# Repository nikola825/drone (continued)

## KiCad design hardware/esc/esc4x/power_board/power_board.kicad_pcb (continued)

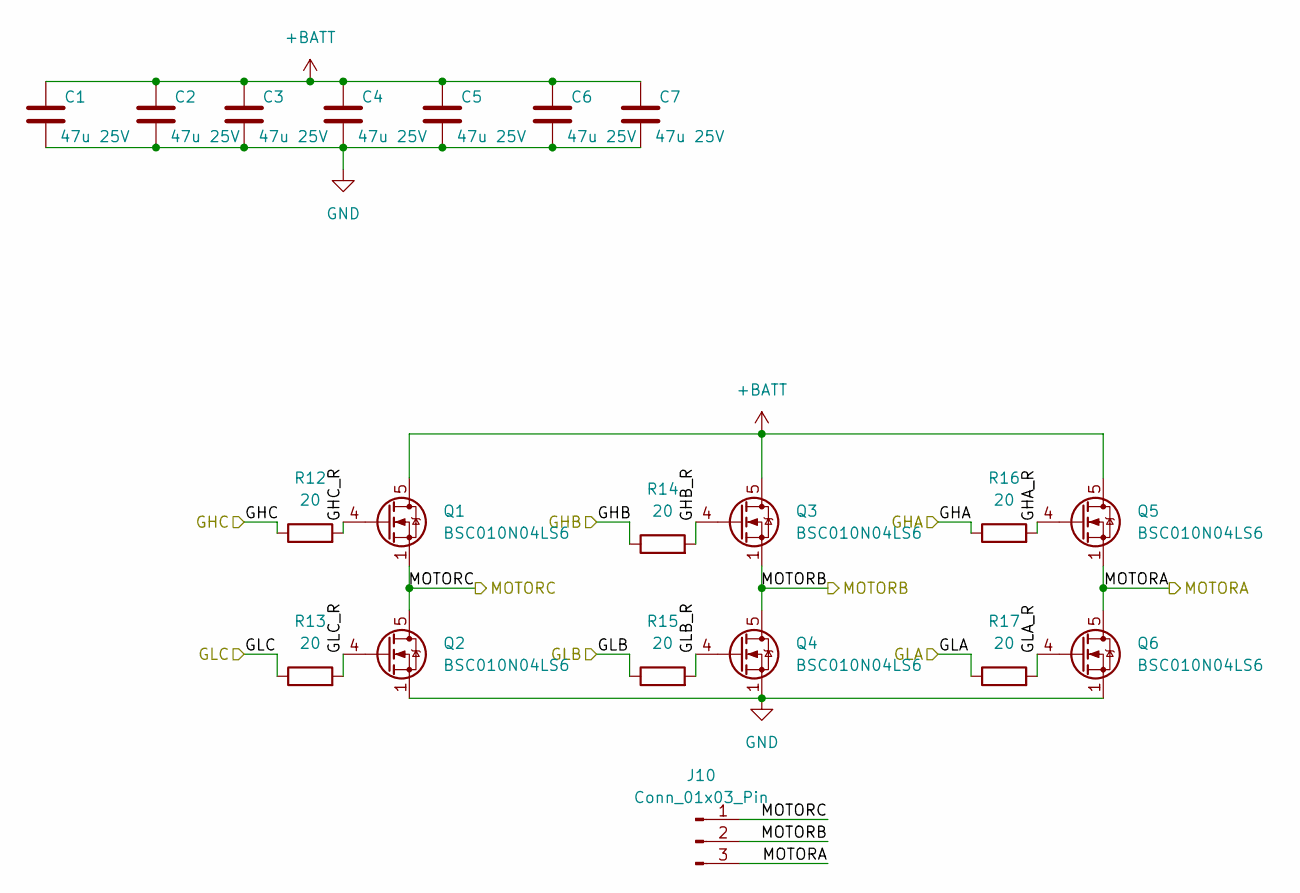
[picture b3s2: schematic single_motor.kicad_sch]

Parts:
C1, C2, C3, C4, C5, C6, C7: 47u 25V; C_1206_3216Metric
J10: Conn_01x03_Pin; EscMotorConnector
Q1, Q2, Q3, Q4, Q5, Q6: BSC010N04LS6; InfineonTdson8FL
R12, R13, R14, R15, R16, R17: 20; R_0402_1005Metric

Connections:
+BATT: C1.1, C2.1, C3.1, C4.1, C5.1, C6.1, C7.1, Q1.5 (D), Q3.5 (D), Q5.5 (D); also elsewhere on the board
/EscMotor1/GHA: R16.1; also elsewhere on the board
/EscMotor1/GHA_R: Q5.4 (G), R16.2
/EscMotor1/GHB: R14.1; also elsewhere on the board
/EscMotor1/GHB_R: Q3.4 (G), R14.2
/EscMotor1/GHC: R12.1; also elsewhere on the board
/EscMotor1/GHC_R: Q1.4 (G), R12.2
/EscMotor1/GLA: R17.1; also elsewhere on the board
/EscMotor1/GLA_R: Q6.4 (G), R17.2
/EscMotor1/GLB: R15.1; also elsewhere on the board
/EscMotor1/GLB_R: Q4.4 (G), R15.2
/EscMotor1/GLC: R13.1; also elsewhere on the board
/EscMotor1/GLC_R: Q2.4 (G), R13.2
/EscMotor1/MOTORA: J10.3, Q5.1 (S), Q6.5 (D); also elsewhere on the board
/EscMotor1/MOTORB: J10.2, Q3.1 (S), Q4.5 (D); also elsewhere on the board
/EscMotor1/MOTORC: J10.1, Q1.1 (S), Q2.5 (D); also elsewhere on the board
GND: C1.2, C2.2, C3.2, C4.2, C5.2, C6.2, C7.2, Q2.1 (S), Q4.1 (S), Q6.1 (S); also elsewhere on the board

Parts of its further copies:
C12, C13, C14, C15, C16, C17, C18, C19, C20, C21, C22, C23, C24, C25, C26, C27, C28, C29, C30, C31, C32: 47u 25V; C_1206_3216Metric
J4, J5, J6: Conn_01x03_Pin; EscMotorConnector
Q7, Q8, Q9, Q10, Q11, Q12, Q13, Q14, Q15, Q16, Q17, Q18, Q19, Q20, Q21, Q22, Q23, Q24: BSC010N04LS6; InfineonTdson8FL
R1, R2, R3, R4, R5, R6, R7, R8, R9, R10, R11, R18, R19, R20, R21, R22, R23, R24: 20; R_0402_1005Metric

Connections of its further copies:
+BATT: C12.1, C13.1, C14.1, C15.1, C16.1, C17.1, C18.1, C19.1, C20.1, C21.1, C22.1, C23.1, C24.1, C25.1, C26.1, C27.1, C28.1, C29.1, C30.1, C31.1, C32.1, Q7.5 (D), Q9.5 (D), Q11.5 (D), Q13.5 (D), Q15.5 (D), Q17.5 (D), Q19.5 (D), Q21.5 (D), Q23.5 (D); also elsewhere on the board
/EscMotor2/GHA: R5.1; also elsewhere on the board
/EscMotor2/GHA_R: Q11.4 (G), R5.2
/EscMotor2/GHB: R3.1; also elsewhere on the board
/EscMotor2/GHB_R: Q9.4 (G), R3.2
/EscMotor2/GHC: R1.1; also elsewhere on the board
/EscMotor2/GHC_R: Q7.4 (G), R1.2
/EscMotor2/GLA: R6.1; also elsewhere on the board
/EscMotor2/GLA_R: Q12.4 (G), R6.2
/EscMotor2/GLB: R4.1; also elsewhere on the board
/EscMotor2/GLB_R: Q10.4 (G), R4.2
/EscMotor2/GLC: R2.1; also elsewhere on the board
/EscMotor2/GLC_R: Q8.4 (G), R2.2
/EscMotor2/MOTORA: J4.3, Q11.1 (S), Q12.5 (D); also elsewhere on the board
/EscMotor2/MOTORB: J4.2, Q9.1 (S), Q10.5 (D); also elsewhere on the board
/EscMotor2/MOTORC: J4.1, Q7.1 (S), Q8.5 (D); also elsewhere on the board
/EscMotor3/GHA: R11.1; also elsewhere on the board
/EscMotor3/GHA_R: Q17.4 (G), R11.2
/EscMotor3/GHB: R9.1; also elsewhere on the board
/EscMotor3/GHB_R: Q15.4 (G), R9.2
/EscMotor3/GHC: R7.1; also elsewhere on the board
/EscMotor3/GHC_R: Q13.4 (G), R7.2
/EscMotor3/GLA: R18.1; also elsewhere on the board
/EscMotor3/GLA_R: Q18.4 (G), R18.2
/EscMotor3/GLB: R10.1; also elsewhere on the board
/EscMotor3/GLB_R: Q16.4 (G), R10.2
/EscMotor3/GLC: R8.1; also elsewhere on the board
/EscMotor3/GLC_R: Q14.4 (G), R8.2
/EscMotor3/MOTORA: J5.3, Q17.1 (S), Q18.5 (D); also elsewhere on the board
/EscMotor3/MOTORB: J5.2, Q15.1 (S), Q16.5 (D); also elsewhere on the board
/EscMotor3/MOTORC: J5.1, Q13.1 (S), Q14.5 (D); also elsewhere on the board
/EscMotor4/GHA: R23.1; also elsewhere on the board
/EscMotor4/GHA_R: Q23.4 (G), R23.2
/EscMotor4/GHB: R21.1; also elsewhere on the board
/EscMotor4/GHB_R: Q21.4 (G), R21.2
/EscMotor4/GHC: R19.1; also elsewhere on the board
/EscMotor4/GHC_R: Q19.4 (G), R19.2
/EscMotor4/GLA: R24.1; also elsewhere on the board
/EscMotor4/GLA_R: Q24.4 (G), R24.2
/EscMotor4/GLB: R22.1; also elsewhere on the board
/EscMotor4/GLB_R: Q22.4 (G), R22.2
/EscMotor4/GLC: R20.1; also elsewhere on the board
/EscMotor4/GLC_R: Q20.4 (G), R20.2
/EscMotor4/MOTORA: J6.3, Q23.1 (S), Q24.5 (D); also elsewhere on the board
/EscMotor4/MOTORB: J6.2, Q21.1 (S), Q22.5 (D); also elsewhere on the board
/EscMotor4/MOTORC: J6.1, Q19.1 (S), Q20.5 (D); also elsewhere on the board
GND: C12.2, C13.2, C14.2, C15.2, C16.2, C17.2, C18.2, C19.2, C20.2, C21.2, C22.2, C23.2, C24.2, C25.2, C26.2, C27.2, C28.2, C29.2, C30.2, C31.2, C32.2, Q8.1 (S), Q10.1 (S), Q12.1 (S), Q14.1 (S), Q16.1 (S), Q18.1 (S), Q20.1 (S), Q22.1 (S), Q24.1 (S); also elsewhere on the board

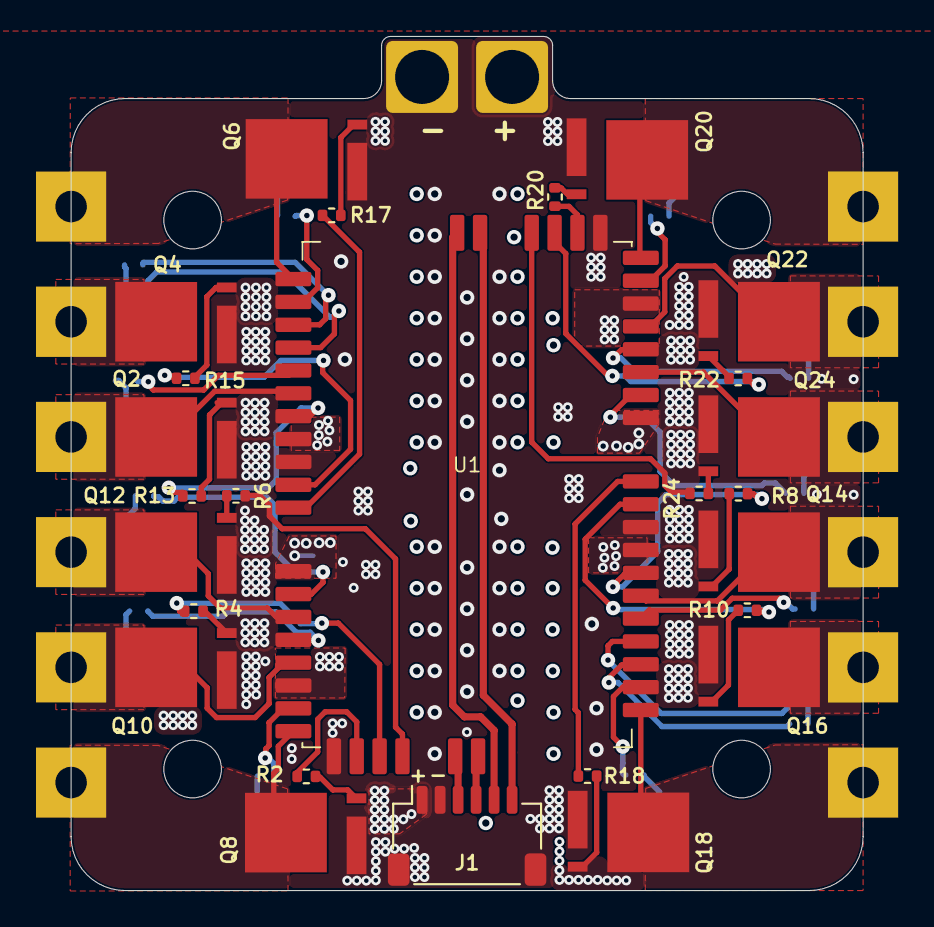
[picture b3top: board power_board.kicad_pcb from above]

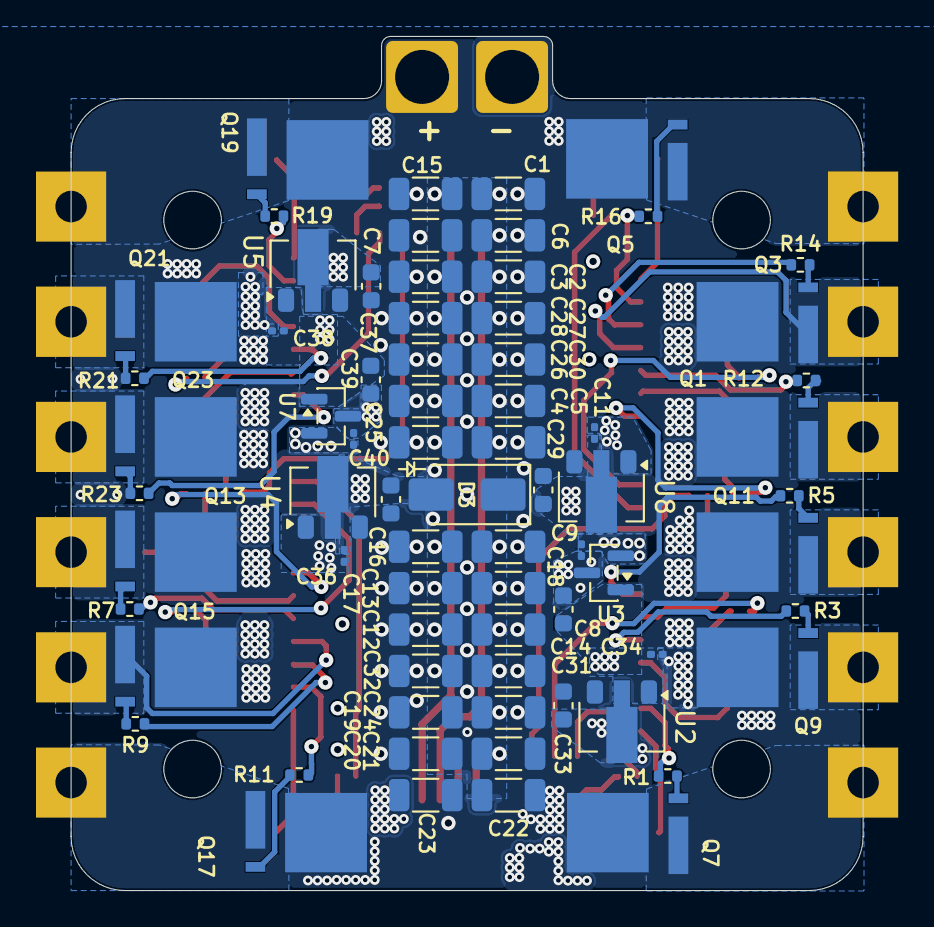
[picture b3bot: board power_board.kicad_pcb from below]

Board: 4 copper layers, 44.0 x 47.5 mm, 107 parts (71 on the bottom side), 72 nets.

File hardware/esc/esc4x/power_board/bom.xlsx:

|  |  | xxxx xxxx xxxxx xxPCS BOM (Sample Bill of Materials)
Item # | *Designator | *Qty | Manufacturer | *Mfg Part # | Description / Value | *Package/Footprint | Type | Your Instructions / Notes
1 | C1, C2, C3, C4, C5, C6, C7, C12, C13, C14, C15, C16, C17, C18, C19, C20, C21, C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 | 28 | TDK | C3216X5R1E476M160AC | CAP CER 47uF 25V X5R 1206 | 1206 | SMD
2 | C8, C10, C33, C35, C37, C39 | 6 | Murata | GCJ188R71E105KA01D | CAP CER 1uF 25V X7R 0603 | 0603 | SMD
3 | C9, C11, C34, C36, C38, C40 | 6 | Murata | GRM033R61A105ME44D | CAP CER 1uF 10V X5R 0201 | 0201 | SMD
4 | D3 | 1 | Yageo | SMAJ26A-HP6AT | VS Diodes SMAJ DO214AC 26V 42.1V AEC-Q101 | DO-214AC | SMD
5 | J1 | 1 | JST | SM06B-SRSS-TB | JST SH Headers SMT SIDE 6-pin | JST SH 6-pin header | SMD
6 | Q1, Q2, Q3, Q4, Q5, Q6, Q7, Q8, Q9, Q10, Q11, Q12, Q13, Q14, Q15, Q16, Q17, Q18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 | 24 | Infineon | BSC010N04LS6 | N-Channel 40 V 100A 3W Surface Mount PG-TDSON-8-6 | TDSON-8-FL | SMD
7 | R1, R2, R3, R4, R5, R6, R7, R8, R9, R10, R11, R12, R13, R14, R15, R16, R17, R18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 | 24 | Yageo | RC0402FR-0720RL | RES 20 OHM 0.067W 1% 0402 | 0402 | SMD
8 | U2, U4, U5, U8 | 4 | Diodes incorporated | AP7381-50Y-13 | LDO Voltage Regulators 150mA 5V | SOT-89-3 | SMD
9 | U3, U7 | 2 | Diodes incorporated | AP7381-33SA-7 | LDO Voltage Regulator 100mA 3.3V | SOT-23-3 | SMD
Need a quick and accurante quote? Need an efficient production? Please read SMT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
Click for Instructions on How to Create a BOM

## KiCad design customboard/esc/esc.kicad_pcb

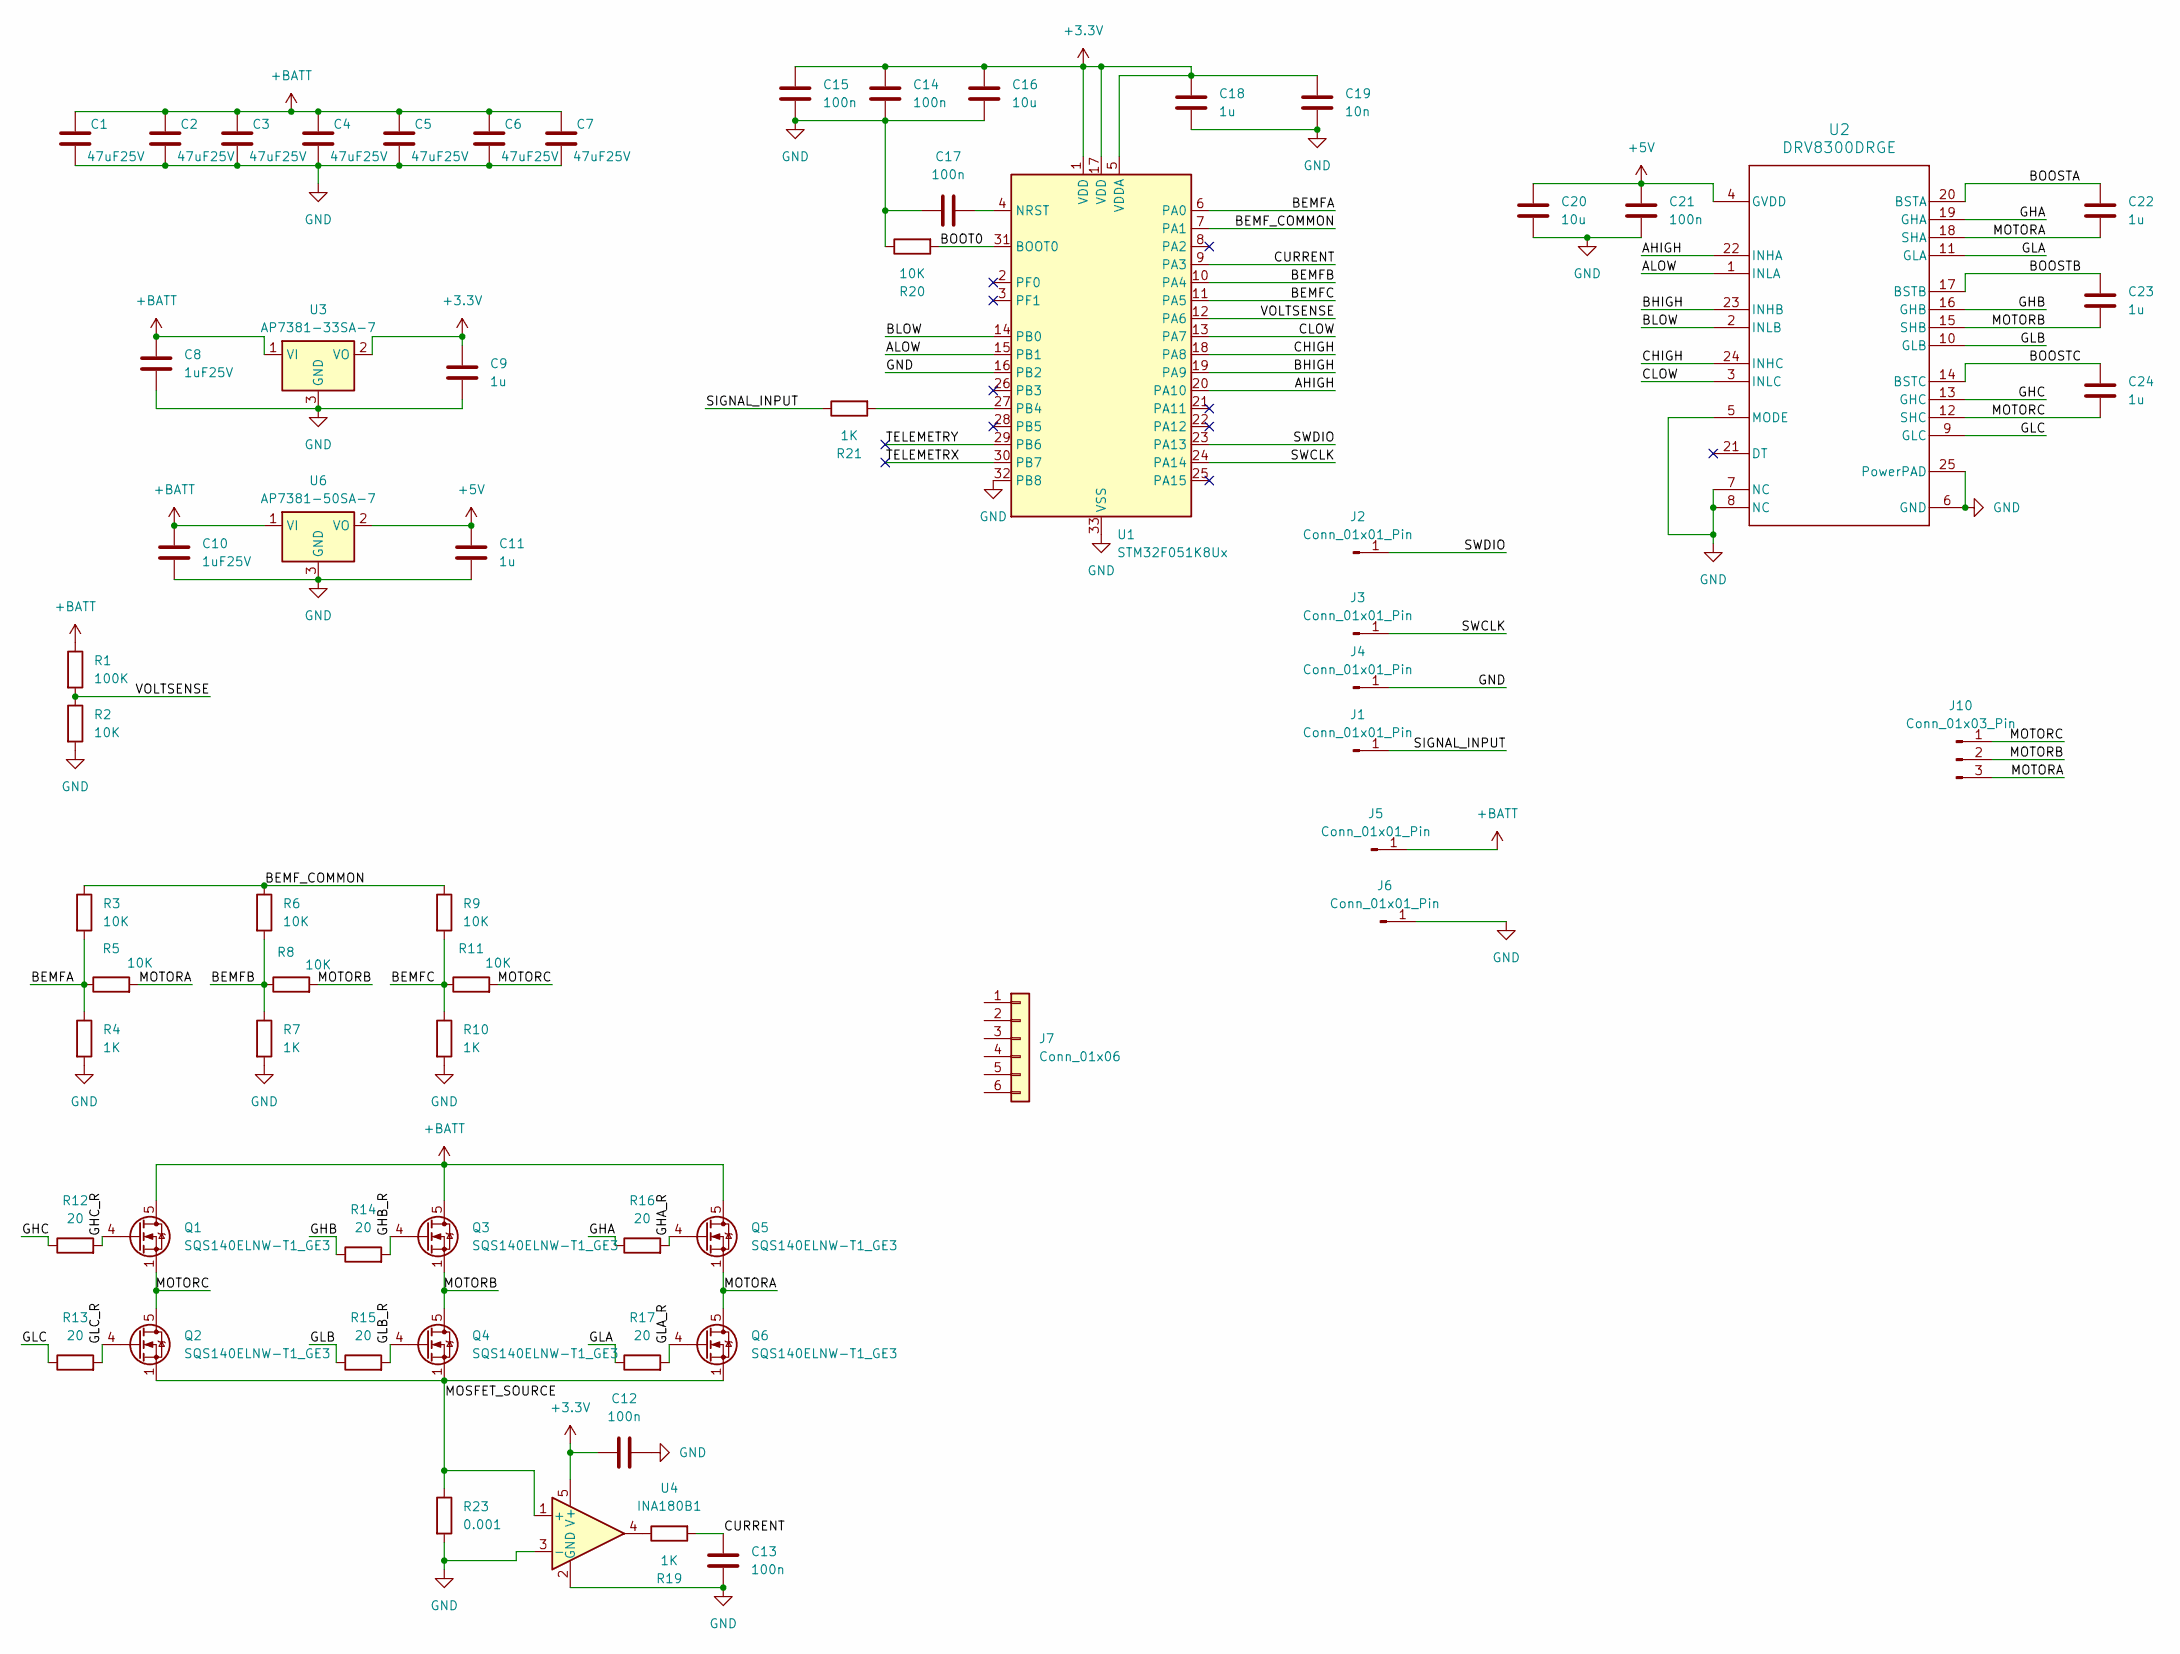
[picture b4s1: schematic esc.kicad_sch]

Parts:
C1, C2, C3, C4, C5, C6, C7: 47uF25V; C_1206_3216Metric
C8, C10: 1uF25V; C_0603_1608Metric
C9, C11, C18, C22, C23, C24: 1u; C_0201_0603Metric
C12, C13, C14, C15, C17, C21: 100n; C_0201_0603Metric
C16, C20: 10u; C_0402_1005Metric
C19: 10n; C_0201_0603Metric
J1, J2, J3, J4: Conn_01x01_Pin; SolderWirePad_1x01_SMD_1x2mm
J5, J6: Conn_01x01_Pin; EscBatteryConnector
J7: Conn_01x06; PinHeader_1x06_P1.27mm_Vertical
J10: Conn_01x03_Pin; EscMotorConnector
Q1, Q2, Q3, Q4, Q5, Q6: SQS140ELNW-T1_GE3; Vishay_PowerPAK_1212-8_Single
R1: 100K; R_0402_1005Metric
R2: 10K; R_0402_1005Metric
R3, R5, R6, R8, R9, R11, R20: 10K; R_0201_0603Metric
R4, R7, R10, R19, R21: 1K; R_0201_0603Metric
R12, R13, R14, R15, R16, R17: 20; R_0402_1005Metric
R23: 0.001; R_2512_6332Metric
U1: STM32F051K8Ux; QFN-32-1EP_5x5mm_P0.5mm_EP3.45x3.45mm-Custom
U2: DRV8300DRGE; VQFN-24-1EP_4x4mm_P0.5mm_EP2.45x2.45mm_ThermalVias-Custom
U3: AP7381-33SA-7; SOT-23
U4: INA180B1; SOT-23-5
U6: AP7381-50SA-7; SOT-23

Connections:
+3.3V: C9.1, C12.1, C14.2, C15.2, C16.2, C18.1, C19.2, U1.1 (VDD), U1.5 (VDDA), U1.17 (VDD), U3.2 (VO), U4.5 (V+)
+5V: C11.1, C20.2, C21.2, U2.4 (GVDD), U6.2 (VO)
+BATT: C1.1, C2.1, C3.1, C4.1, C5.1, C6.1, C7.1, C8.1, C10.1, J5.1, Q1.5 (D), Q3.5 (D), Q5.5 (D), R1.1, U3.1 (VI), U6.1 (VI)
/AHIGH: U1.20 (PA10), U2.22 (INHA)
/ALOW: U1.15 (PB1), U2.1 (INLA)
/BEMFA: R3.2, R4.1, R5.1, U1.6 (PA0)
/BEMFB: R6.2, R7.1, R8.1, U1.10 (PA4)
/BEMFC: R9.2, R10.1, R11.1, U1.11 (PA5)
/BEMF_COMMON: R3.1, R6.1, R9.1, U1.7 (PA1)
/BHIGH: U1.19 (PA9), U2.23 (INHB)
/BLOW: U1.14 (PB0), U2.2 (INLB)
/BOOSTA: C22.2, U2.20 (BSTA)
/BOOSTB: C23.2, U2.17 (BSTB)
/BOOSTC: C24.2, U2.14 (BSTC)
/BOOT0: R20.2, U1.31 (BOOT0)
/CHIGH: U1.18 (PA8), U2.24 (INHC)
/CLOW: U1.13 (PA7), U2.3 (INLC)
/CURRENT: C13.2, R19.2, U1.9 (PA3)
/GHA: R16.1, U2.19 (GHA)
/GHA_R: Q5.4 (G), R16.2
/GHB: R14.1, U2.16 (GHB)
/GHB_R: Q3.4 (G), R14.2
/GHC: R12.1, U2.13 (GHC)
/GHC_R: Q1.4 (G), R12.2
/GLA: R17.1, U2.11 (GLA)
/GLA_R: Q6.4 (G), R17.2
/GLB: R15.1, U2.10 (GLB)
/GLB_R: Q4.4 (G), R15.2
/GLC: R13.1, U2.9 (GLC)
/GLC_R: Q2.4 (G), R13.2
/MOSFET_SOURCE: Q2.1 (S), Q2.2 (S), Q2.3 (S), Q4.1 (S), Q4.2 (S), Q4.3 (S), Q6.1 (S), Q6.2 (S), Q6.3 (S), R23.1, U4.1 (+)
/MOTORA: C22.1, J10.3, Q5.1 (S), Q5.2 (S), Q5.3 (S), Q6.5 (D), R5.2, U2.18 (SHA)
/MOTORB: C23.1, J10.2, Q3.1 (S), Q3.2 (S), Q3.3 (S), Q4.5 (D), R8.2, U2.15 (SHB)
/MOTORC: C24.1, J10.1, Q1.1 (S), Q1.2 (S), Q1.3 (S), Q2.5 (D), R11.2, U2.12 (SHC)
/SIGNAL_INPUT: J1.1, R21.1
/SWCLK: J3.1, U1.24 (PA14)
/SWDIO: J2.1, U1.23 (PA13)
/TELEMETRX: U1.30 (PB7)
/TELEMETRY: U1.29 (PB6)
/VOLTSENSE: R1.2, R2.1, U1.12 (PA6)
GND: C1.2, C2.2, C3.2, C4.2, C5.2, C6.2, C7.2, C8.2, C9.2, C10.2, C11.2, C12.2, C13.1, C14.1, C15.1, C16.1, C17.2, C18.2, C19.1, C20.1, C21.1, J4.1, J6.1, R2.2, R4.2, R7.2, R10.2, R20.1, R23.2, U1.16 (PB2), U1.32 (PB8), U1.33 (VSS), U2.5 (MODE), U2.6 (GND), U2.7 (NC), U2.8 (NC), U2.25 (PowerPAD), U3.3 (GND), U4.2 (GND), U4.3 (-), U6.3 (GND)
unnamed: R19.1, U4.4
unnamed: C17.1, U1.4 (NRST)
unnamed: R21.2, U1.27 (PB4)

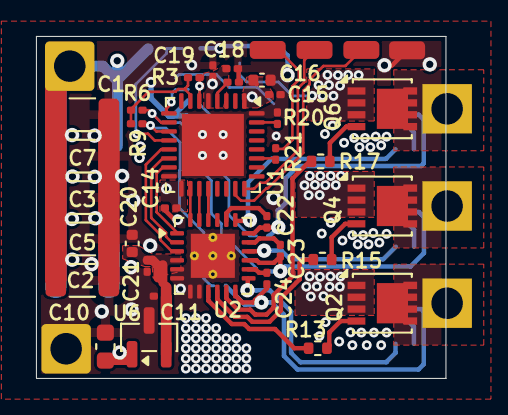
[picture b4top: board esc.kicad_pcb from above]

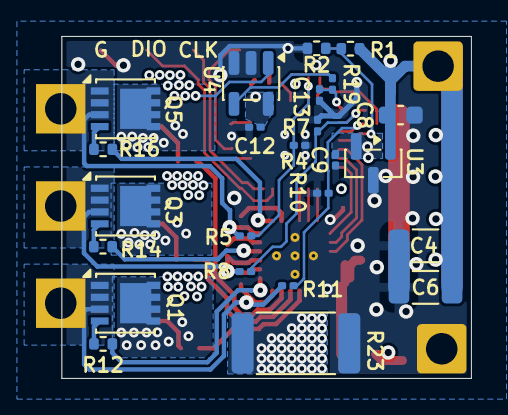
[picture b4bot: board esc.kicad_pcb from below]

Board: 4 copper layers, 22.8 x 19.0 mm, 63 parts (25 on the bottom side), 42 nets.

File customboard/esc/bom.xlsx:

|  |  | xxxx xxxx xxxxx xxPCS BOM (Sample Bill of Materials)
Item # | *Designator | *Qty | Manufacturer | *Mfg Part # | Description / Value | *Package/Footprint | Type | Your Instructions / Notes
1 | C1, C2, C3, C4, C5, C6, C7 | 7 | TDK | C3216X5R1E476M160AC | CAP CER 47uF 25V X5R 1206 | 1206 | SMD
2 | C10, C8 | 2 | Murata | GCJ188R71E105KA01D | CAP CER 1uF 25V X7R 0603 | 0603 | SMD
3 | C11, C18, C22, C23, C24, C9 | 6 | Murata | GRM033R61A105ME44D | CAP CER 1uF 10V X5R 0201 | 0201 | SMD
4 | C12, C13, C14, C15, C17, C21 | 6 | Murata | GRM033R61A104KE15D | CAP CER 100nF 10V X5R 0201 | 0201 | SMD
5 | Q1, Q2, Q3, Q4, Q5, Q6 | 6 | Vishay | SQS140ELNW-T1_GE3 | N-Channel 40 V 153A 119W Surface Mount, PowerPAK 1212-8SLW | PowerPAK 1212-8SLW | SMD
6 | R1 | 1 | Yageo | RC0402FR-7D100KL | RES 100K OHM 0.067W 1% 0402 | 0402 | SMD
7 | R2 | 1 | Yageo | RC0402FR-7D10KL | RES 10K OHM 0.067W 1% 0402 | 0402 | SMD
8 | R10, R19, R21, R4, R7 | 5 | Yageo | RC0201FR-071KL | RES 1K OHM 0.05W 1% 0201 | 0201 | SMD
9 | R11, R20, R3, R5, R6, R8, R9 | 7 | Yageo | RC0201FR-0710KL | RES 10K OHM 0.05W 1% 0201 | 0201 | SMD
10 | R12, R13, R14, R15, R16, R17 | 6 | Yageo | RC0402FR-0720RL | RES 20 OHM 0.067W 1% 0402 | 0402 | SMD
11 | R23 | 1 | Yageo | PU2512FKNP50R001L | RES 1m OHM 5W 1% 2512 | 2512 | SMD
12 | U3 | 1 | Diodes incorporated | AP7381-33SA-7 | LDO Voltage Regulator 100mA 3.3V | SOT-23-3 | SMD
13 | U4 | 1 | Texas instruments | INA180B1IDBVR | Current Sense Amplifiers 26V 350kHz current sense amplifier | SOT-23-5 | SMD
14 | C16, C20 | 2 | Samsung | CL05A106MP5NUNC | CAP CER 10uF 10V X5R 0402 | 0402 | SMD
15 | C19 | 1 | Murata | GRM033R61C103KA12D | CAP CER 10nF 16V X5R 0201 | 0201 | SMD
16 | U1 | 1 | STMicroelectronics | STM32F051K8U6TR | ARM Microcontrollers - MCU ARM Cortex-M0 MCU 64Kb Flash 48MHz | UFQFPN-32 | SMD
17 | U2 | 1 | Texas instruments | DRV8300DRGER | Gate Drivers 100-V max simple 3-p hase gate driver | VQFN-24 | SMD
18 | U6 | 1 | Diodes incorporated | AP7381-50SA-7 | LDO Voltage Regulator 100mA 5V | SOT-23-3 | SMD
Need a quick and accurante quote? Need an efficient production? Please read SMT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
Click for Instructions on How to Create a BOM

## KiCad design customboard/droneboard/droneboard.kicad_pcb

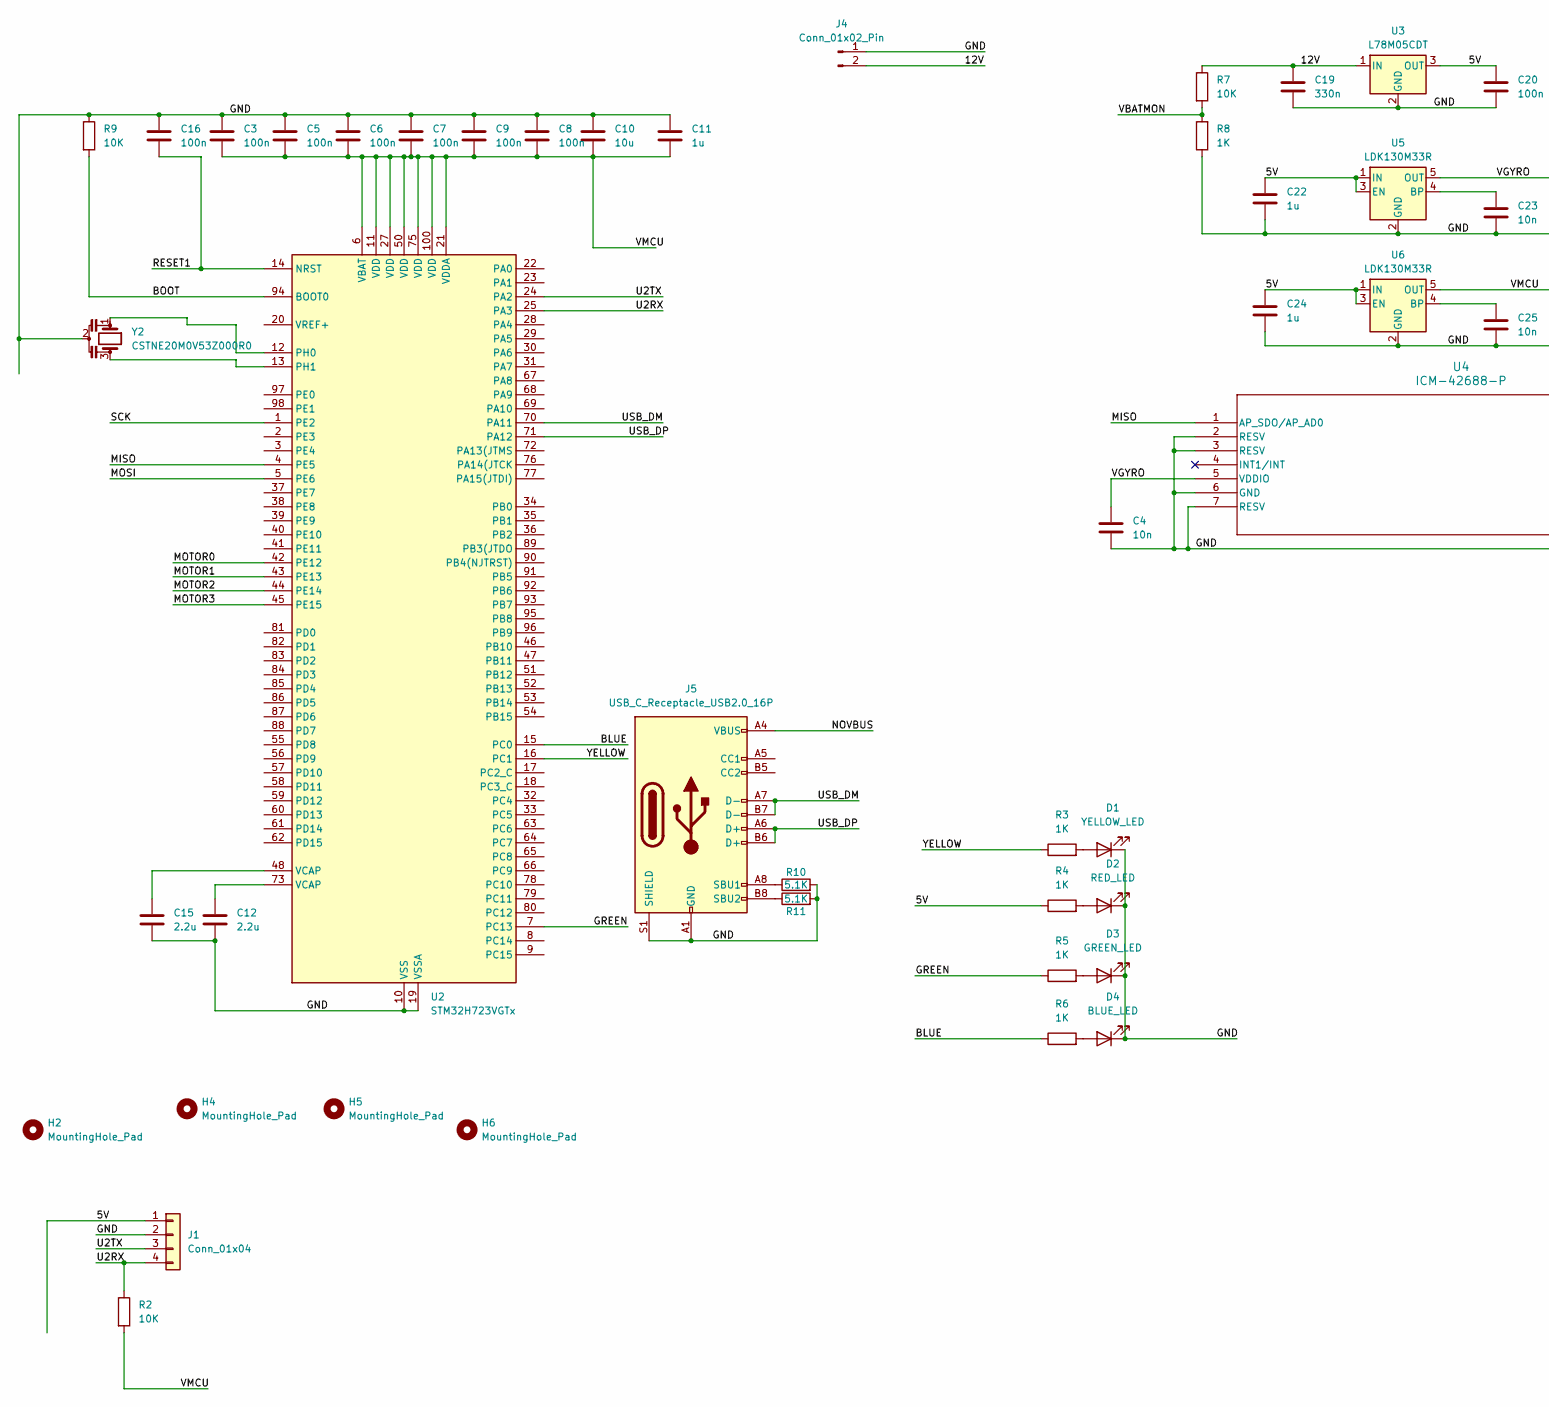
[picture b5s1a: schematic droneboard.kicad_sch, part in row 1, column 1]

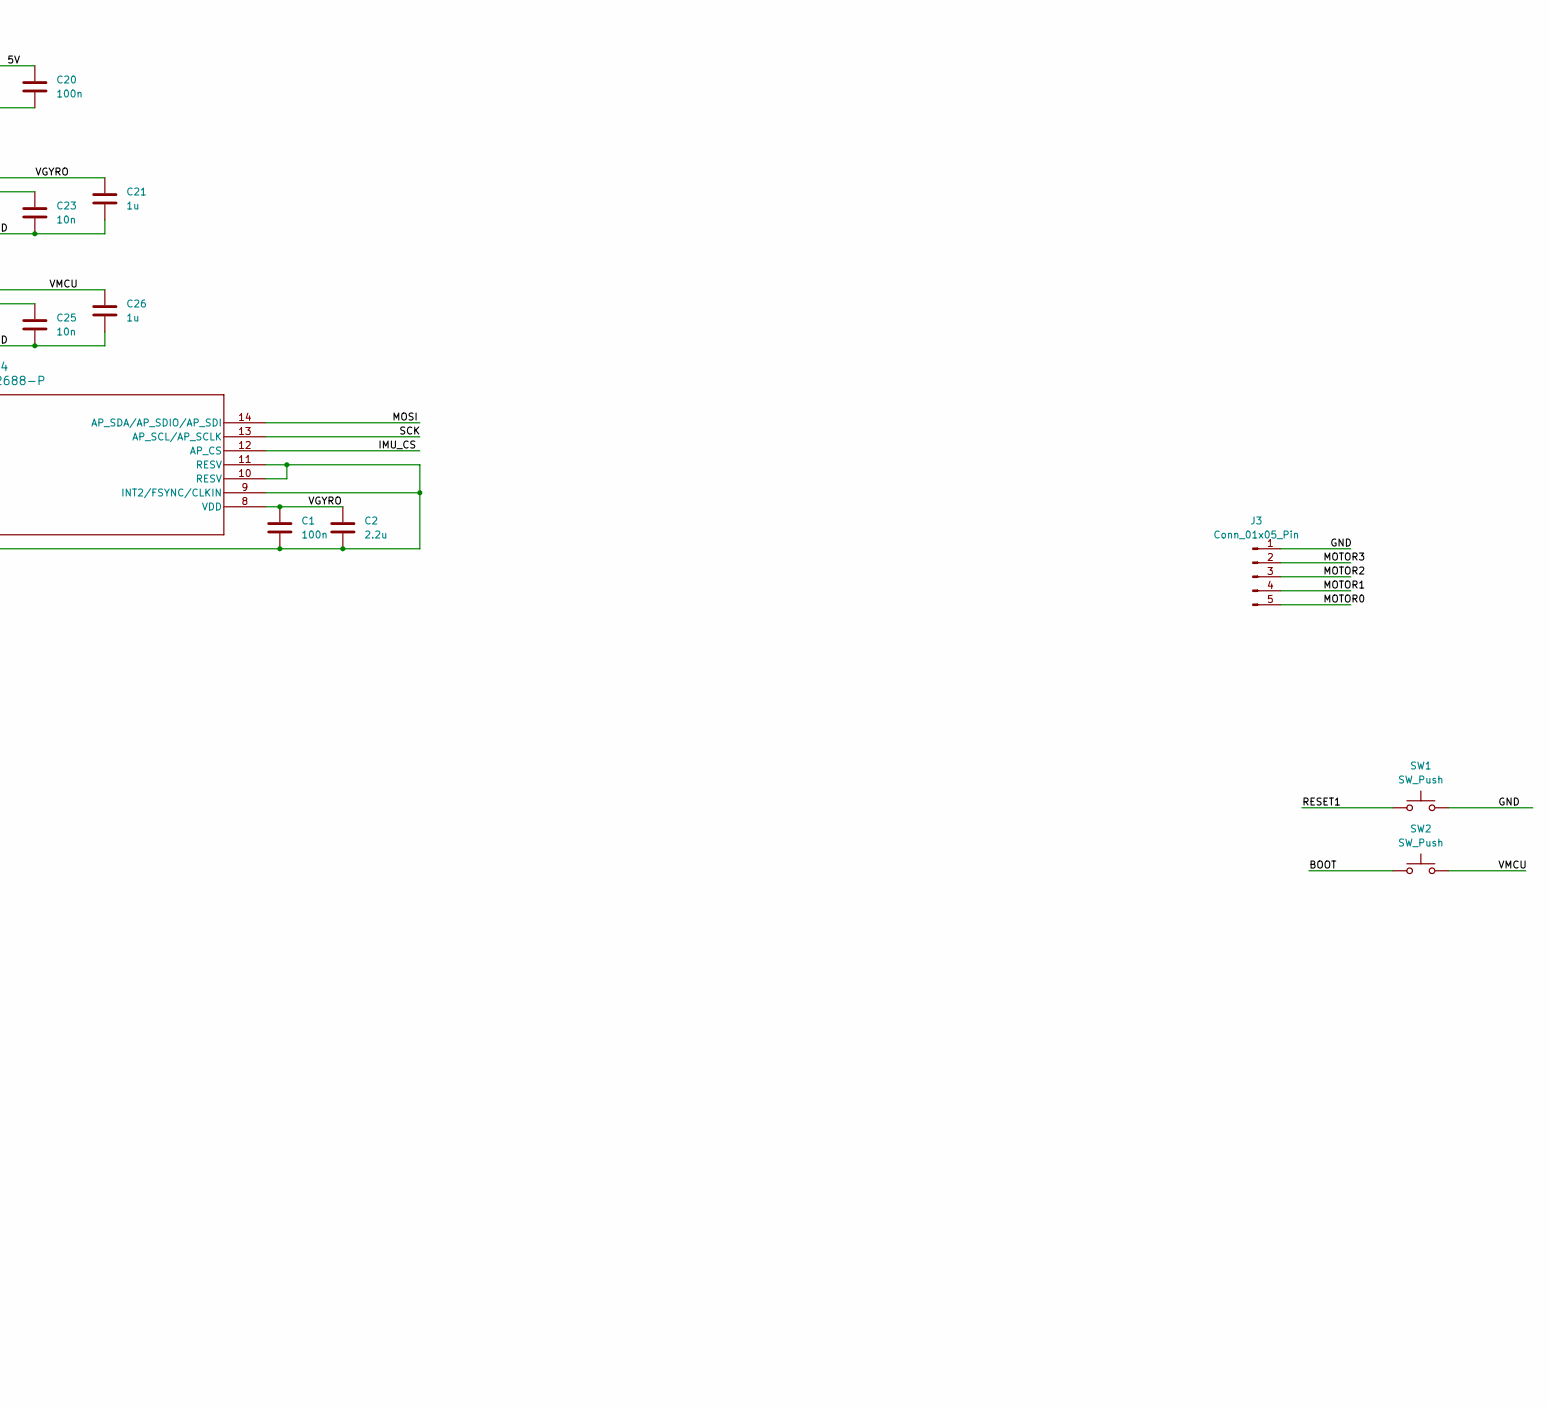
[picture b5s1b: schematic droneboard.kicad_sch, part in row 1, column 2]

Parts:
C1, C3, C5, C6, C7, C8, C9, C16: 100n; C_0201_0603Metric
C2, C12, C15: 2.2u; C_0201_0603Metric
C4, C23, C25: 10n; C_0201_0603Metric
C10: 10u; C_0402_1005Metric
C11, C21, C22, C24, C26: 1u; C_0201_0603Metric
C19: 330n; C_0805_2012Metric
C20: 100n; C_0603_1608Metric
D1: YELLOW_LED; LED_0603_1608Metric
D2: RED_LED; LED_0603_1608Metric
D3: GREEN_LED; LED_0603_1608Metric
D4: BLUE_LED; LED_0603_1608Metric
H2, H4, H5, H6: MountingHole_Pad; MountingHole_4.3mm_M4_DIN965
J1: Conn_01x04; PinHeader_1x04_P1.27mm_Vertical
J3: Conn_01x05_Pin; PinHeader_1x05_P1.27mm_Vertical
J4: Conn_01x02_Pin; PinHeader_1x02_P1.27mm_Vertical
J5: USB_C_Receptacle_USB2.0_16P; USB_C_Receptacle_GCT_USB4110
R2, R7: 10K; R_0402_1005Metric
R3, R4, R5, R6, R8: 1K; R_0402_1005Metric
R9: 10K; R_0201_0603Metric
R10, R11: 5.1K; R_0201_0603Metric
SW1, SW2: SW_Push; SW_PUSH_1P1T_6x3.5mm_H4.3_APEM_MJTP1243
U2: STM32H723VGTx; LQFP-100_14x14mm_P0.5mm
U3: L78M05CDT; TO-252-2
U4: ICM-42688-P; LGA14_2P5X3X0P91_IVS-L
U5, U6: LDK130M33R; SOT-23-5
Y2: CSTNE20M0V53Z000R0; Resonator_SMD_Murata_CSTxExxV-3Pin_3.0x1.1mm

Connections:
/5V: C20.2, C22.1, C24.1, J1.1, R4.1, U3.3 (OUT), U5.1 (IN), U5.3 (EN), U6.1 (IN), U6.3 (EN)
/12V: C19.2, J4.2, R7.1, U3.1 (IN)
/BLUE: R6.1, U2.15 (PC0)
/BOOT: R9.2, SW2.1, U2.94 (BOOT0)
/GND: C1.1, C2.2, C3.2, C4.1, C5.2, C6.2, C7.2, C8.2, C9.2, C10.1, C11.1, C12.2, C15.2, C16.2, C19.1, C20.1, C21.2, C22.2, C23.1, C24.2, C25.1, C26.2, D1.1 (K), D2.1 (K), D3.1 (K), D4.1 (K), J1.2, J3.1, J4.1, J5.A1 (GND), J5.A12 (GND), J5.B1 (GND), J5.B12 (GND), J5.S1 (SHIELD), R8.1, R9.1, R10.2, R11.2, SW1.2, U2.10 (VSS), U2.19 (VSSA), U2.26 (VSS), U2.49 (VSS), U2.74 (VSS), U2.99 (VSS), U3.2 (GND), U4.2 (RESV), U4.3 (RESV), U4.6 (GND), U4.7 (RESV), U4.9 (INT2/FSYNC/CLKIN), U4.10 (RESV), U4.11 (RESV), U5.2 (GND), U6.2 (GND), Y2.2
/GREEN: R5.1, U2.7 (PC13)
/IMU_CS: U4.12 (AP_CS)
/MISO: U2.4 (PE5), U4.1 (AP_SDO/AP_AD0)
/MOSI: U2.5 (PE6), U4.14 (AP_SDA/AP_SDIO/AP_SDI)
/MOTOR0: J3.5, U2.42 (PE12)
/MOTOR1: J3.4, U2.43 (PE13)
/MOTOR2: J3.3, U2.44 (PE14)
/MOTOR3: J3.2, U2.45 (PE15)
/NOVBUS: J5.A4 (VBUS), J5.A9 (VBUS), J5.B4 (VBUS), J5.B9 (VBUS)
/RESET1: C16.1, SW1.1, U2.14 (NRST)
/SCK: U2.1 (PE2), U4.13 (AP_SCL/AP_SCLK)
/U2RX: J1.4, R2.1, U2.25 (PA3)
/U2TX: J1.3, U2.24 (PA2)
/USB_DM: J5.A7 (D-), J5.B7 (D-), U2.70 (PA11)
/USB_DP: J5.A6 (D+), J5.B6 (D+), U2.71 (PA12)
/VBATMON: R7.2, R8.2
/VGYRO: C1.2, C2.1, C4.2, C21.1, U4.5 (VDDIO), U4.8 (VDD), U5.5 (OUT)
/VMCU: C3.1, C5.1, C6.1, C7.1, C8.1, C9.1, C10.2, C11.2, C26.1, R2.2, SW2.2, U2.6 (VBAT), U2.11 (VDD), U2.21 (VDDA), U2.27 (VDD), U2.50 (VDD), U2.75 (VDD), U2.100 (VDD), U6.5 (OUT)
/YELLOW: R3.1, U2.16 (PC1)
unnamed: C12.1, U2.73 (VCAP)
unnamed: C15.1, U2.48 (VCAP)
unnamed: D1.2 (A), R3.2
unnamed: D2.2 (A), R4.2
unnamed: D3.2 (A), R5.2
unnamed: D4.2 (A), R6.2
unnamed: J5.A8 (SBU1), R10.1
unnamed: J5.B8 (SBU2), R11.1
unnamed: U2.12 (PH0), Y2.1
unnamed: U2.13 (PH1), Y2.3
unnamed: C23.2, U5.4 (BP)
unnamed: C25.2, U6.4 (BP)

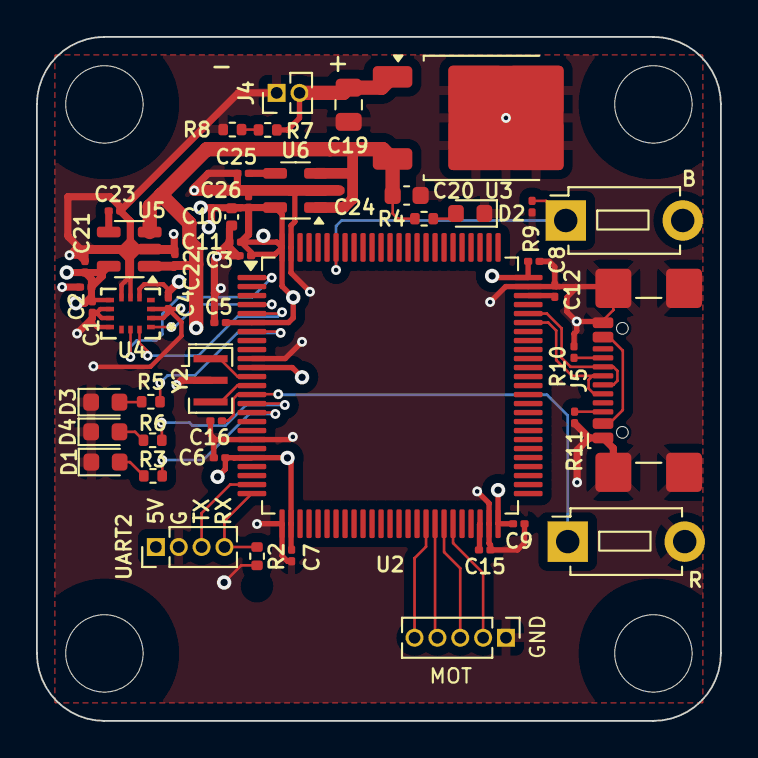
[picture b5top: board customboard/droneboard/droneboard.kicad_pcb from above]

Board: 4 copper layers, 38.0 x 38.0 mm, 52 parts (0 on the bottom side), 35 nets.

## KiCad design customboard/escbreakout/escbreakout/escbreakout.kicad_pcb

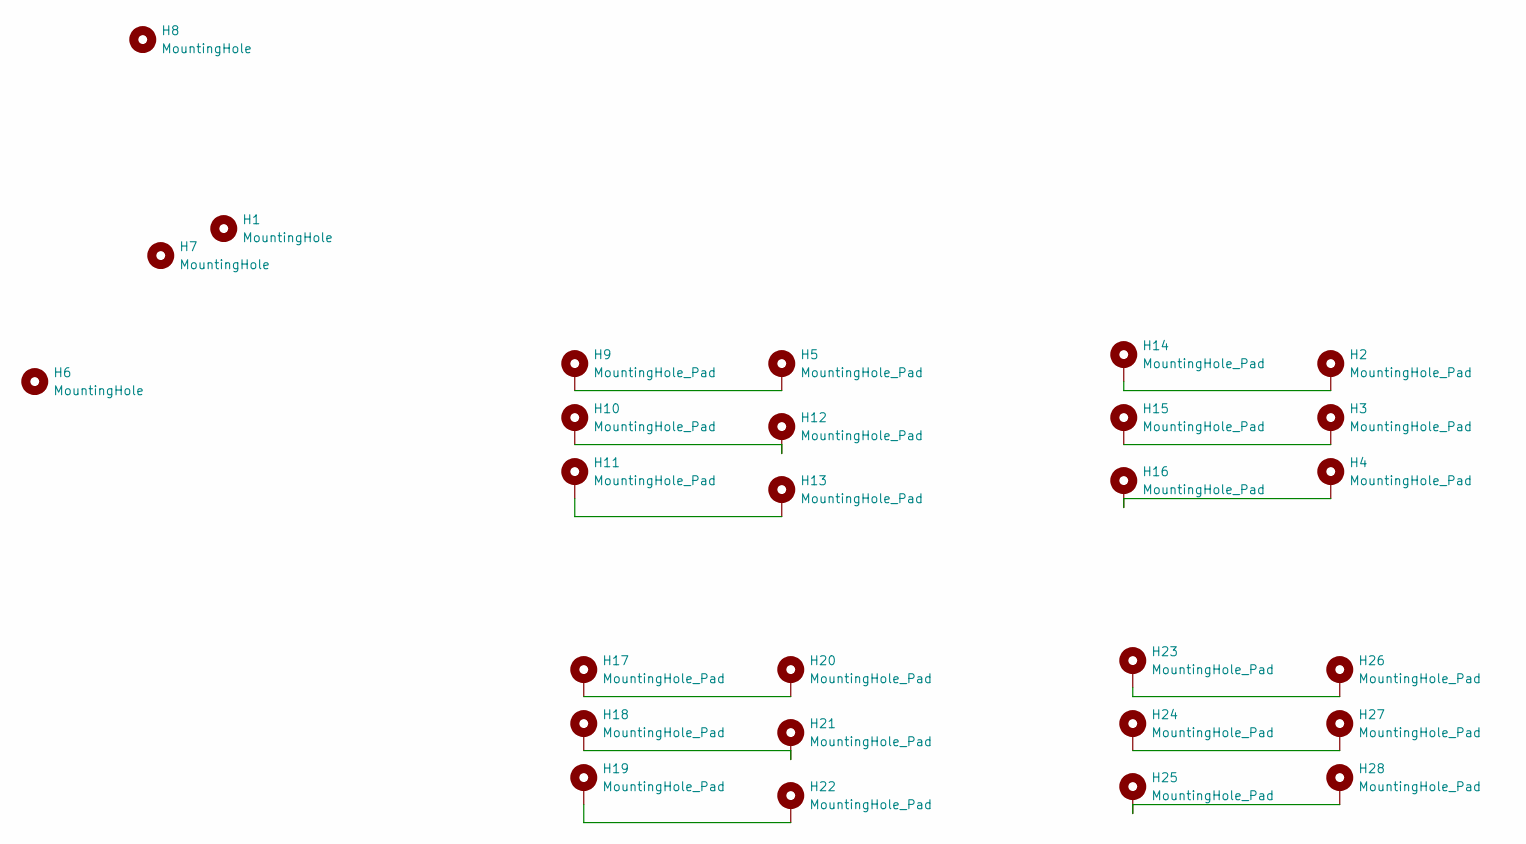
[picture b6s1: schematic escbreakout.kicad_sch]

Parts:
H1, H6, H7, H8: MountingHole; MountingHole_3.2mm_M3
H2, H3, H4, H9, H10, H11, H17, H18, H19, H26, H27, H28: MountingHole_Pad; MountingHole_3.2mm_M3_DIN965_Pad
H5, H12, H13, H14, H15, H16, H20, H21, H22, H23, H24, H25: MountingHole_Pad; ESCPAD

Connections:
unnamed: H5.1, H9.1
unnamed: H10.1, H12.1
unnamed: H11.1, H13.1
unnamed: H2.1, H14.1
unnamed: H3.1, H15.1
unnamed: H4.1, H16.1
unnamed: H17.1, H20.1
unnamed: H18.1, H21.1
unnamed: H19.1, H22.1
unnamed: H23.1, H26.1
unnamed: H24.1, H27.1
unnamed: H25.1, H28.1
